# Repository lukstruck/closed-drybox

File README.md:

# closed-drybox
Open Source Filament Dry Box. But it's closed so it stays dry. Here are the plans, schematics and 3D Models needed.

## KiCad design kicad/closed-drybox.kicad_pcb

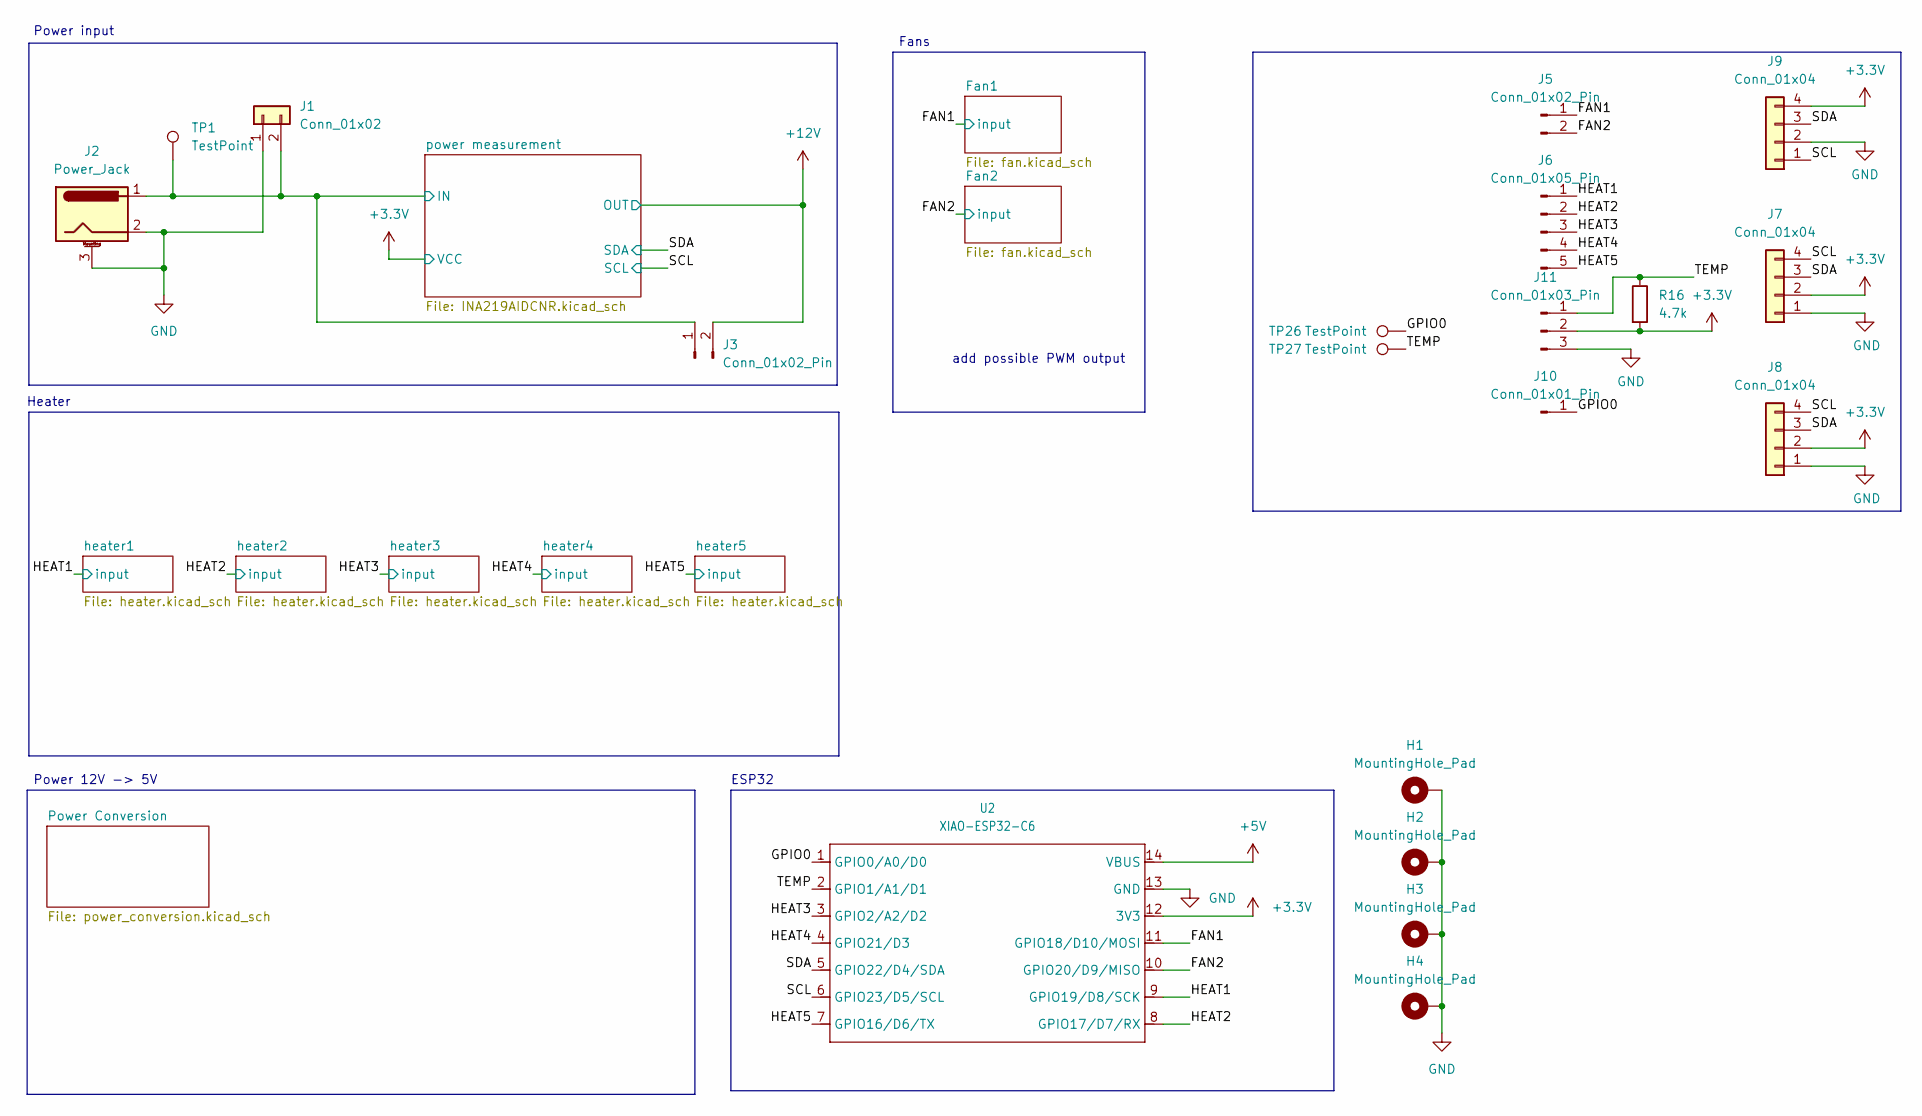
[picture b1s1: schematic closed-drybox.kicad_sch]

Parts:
H1, H2, H3, H4: MountingHole_Pad; MountingHole_3.2mm_M3_DIN965_Pad
J1: Conn_01x02; JST_XH_S2B-XH-A-1_1x02_P2.50mm_Horizontal; LCSC C157931
J2: Power_Jack; BarrelJack_Horizontal; LCSC C720558
J3, J5: Conn_01x02_Pin; PinHeader_1x02_P2.54mm_Vertical
J6: Conn_01x05_Pin; PinHeader_1x05_P2.54mm_Vertical
J7, J8, J9: Conn_01x04; JST_XH_B4B-XH-A_1x04_P2.50mm_Vertical
J10: Conn_01x01_Pin; PinHeader_1x01_P2.54mm_Vertical
J11: Conn_01x03_Pin; PinHeader_1x03_P2.54mm_Vertical
R16: 4.7k; R_0603_1608Metric_Pad0.98x0.95mm_HandSolder
TP1, TP26, TP27: TestPoint; TestPoint_Pad_D2.5mm
U2: XIAO-ESP32-C6; XIAO-ESP32C6-DIP

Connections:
+3.3V: J7.2, J8.2, J9.4, J11.2, R16.2, U2.12 (3V3); also elsewhere on the board
+5V: U2.14 (VBUS)
+12V: J3.2; also elsewhere on the board
/FAN1: J5.1, U2.11 (GPIO18/D10/MOSI); also elsewhere on the board
/FAN2: J5.2, U2.10 (GPIO20/D9/MISO); also elsewhere on the board
/GPIO0: J10.1, TP26.1, U2.1 (GPIO0/A0/D0)
/HEAT1: J6.1, U2.9 (GPIO19/D8/SCK); also elsewhere on the board
/HEAT2: J6.2, U2.8 (GPIO17/D7/RX); also elsewhere on the board
/HEAT3: J6.3, U2.3 (GPIO2/A2/D2); also elsewhere on the board
/HEAT4: J6.4, U2.4 (GPIO21/D3); also elsewhere on the board
/HEAT5: J6.5, U2.7 (GPIO16/D6/TX); also elsewhere on the board
/SCL: J7.4, J8.4, J9.1, U2.6 (GPIO23/D5/SCL); also elsewhere on the board
/SDA: J7.3, J8.3, J9.3, U2.5 (GPIO22/D4/SDA); also elsewhere on the board
/TEMP: J11.1, R16.1, TP27.1, U2.2 (GPIO1/A1/D1)
/power measurement/IN: J1.2, J2.1, J3.1, TP1.1; also elsewhere on the board
GND: H1.1, H2.1, H3.1, H4.1, J1.1, J2.2, J2.3 (MountPin), J7.1, J8.1, J9.2, J11.3, U2.13 (GND); also elsewhere on the board

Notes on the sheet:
add possible PWM output
Heater
ESP32
Power input
Power 12V -> 5V
Fans

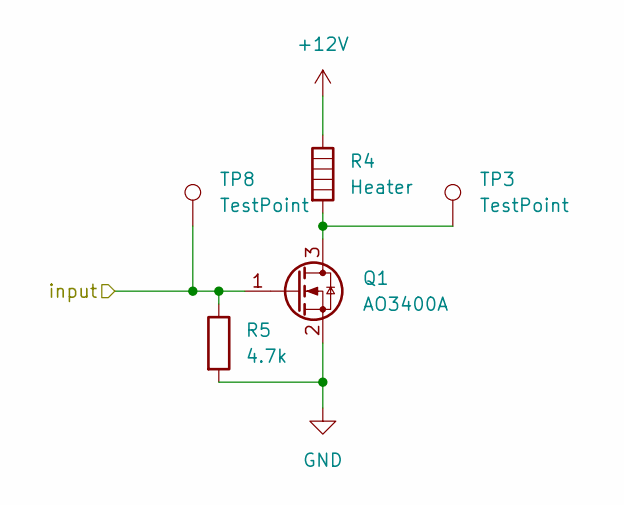
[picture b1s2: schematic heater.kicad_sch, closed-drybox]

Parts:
Q1: AO3400A; SOT-23; LCSC C20917
R4: Heater; JST_XH_S2B-XH-A_1x02_P2.50mm_Horizontal; LCSC C157931
R5: 4.7k; R_0603_1608Metric_Pad0.98x0.95mm_HandSolder
TP3, TP8: TestPoint; TestPoint_Pad_D2.5mm

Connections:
+12V: R4.1; also elsewhere on the board
/HEAT1: Q1.1 (G), R5.1, TP8.1; also elsewhere on the board
GND: Q1.2 (S), R5.2; also elsewhere on the board
unnamed: Q1.3 (D), R4.2, TP3.1

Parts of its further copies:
Q2, Q3, Q4, Q5: AO3400A; SOT-23; LCSC C20917
R6, R8, R10, R12: Heater; JST_XH_S2B-XH-A_1x02_P2.50mm_Horizontal; LCSC C157931
R7, R9, R11, R13: 4.7k; R_0603_1608Metric_Pad0.98x0.95mm_HandSolder
TP4, TP5, TP6, TP7, TP9, TP10, TP11, TP12: TestPoint; TestPoint_Pad_D2.5mm

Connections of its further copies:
+12V: R6.1, R8.1, R10.1, R12.1; also elsewhere on the board
/HEAT2: Q2.1 (G), R7.1, TP9.1; also elsewhere on the board
/HEAT3: Q3.1 (G), R9.1, TP10.1; also elsewhere on the board
/HEAT4: Q4.1 (G), R11.1, TP11.1; also elsewhere on the board
/HEAT5: Q5.1 (G), R13.1, TP12.1; also elsewhere on the board
GND: Q2.2 (S), Q3.2 (S), Q4.2 (S), Q5.2 (S), R7.2, R9.2, R11.2, R13.2; also elsewhere on the board
unnamed: Q2.3 (D), R6.2, TP4.1
unnamed: Q3.3 (D), R8.2, TP5.1
unnamed: Q4.3 (D), R10.2, TP6.1
unnamed: Q5.3 (D), R12.2, TP7.1

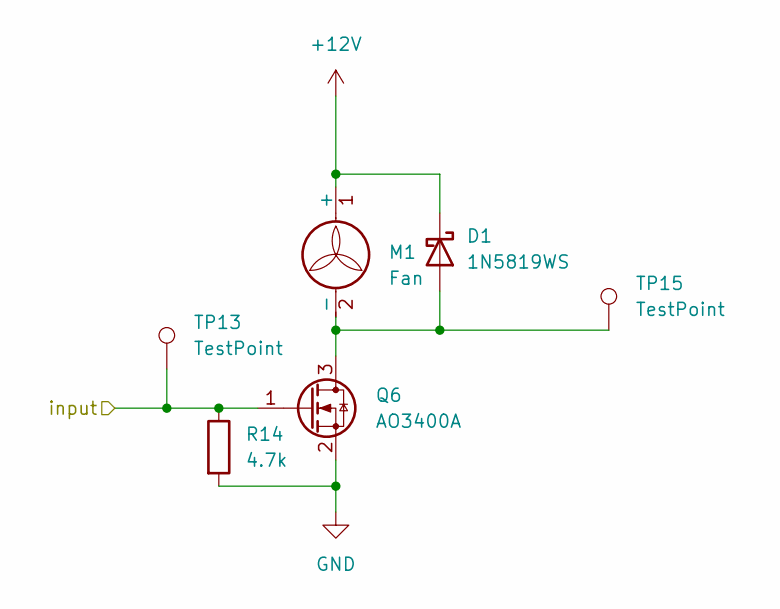
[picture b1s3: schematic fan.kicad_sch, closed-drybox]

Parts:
D1: 1N5819WS; D_SOD-323; LCSC C191023
M1: Fan; JST_XH_S2B-XH-A_1x02_P2.50mm_Horizontal; LCSC C157931
Q6: AO3400A; SOT-23; LCSC C20917
R14: 4.7k; R_0603_1608Metric_Pad0.98x0.95mm_HandSolder
TP13, TP15: TestPoint; TestPoint_Pad_D2.5mm

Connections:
+12V: D1.1 (K), M1.1 (+); also elsewhere on the board
/FAN1: Q6.1 (G), R14.1, TP13.1; also elsewhere on the board
GND: Q6.2 (S), R14.2; also elsewhere on the board
unnamed: D1.2 (A), M1.2 (-), Q6.3 (D), TP15.1

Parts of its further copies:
D2: 1N5819WS; D_SOD-323; LCSC C191023
M2: Fan; JST_XH_S2B-XH-A_1x02_P2.50mm_Horizontal; LCSC C157931
Q7: AO3400A; SOT-23; LCSC C20917
R15: 4.7k; R_0603_1608Metric_Pad0.98x0.95mm_HandSolder
TP14, TP16: TestPoint; TestPoint_Pad_D2.5mm

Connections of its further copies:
+12V: D2.1 (K), M2.1 (+); also elsewhere on the board
/FAN2: Q7.1 (G), R15.1, TP14.1; also elsewhere on the board
GND: Q7.2 (S), R15.2; also elsewhere on the board
unnamed: D2.2 (A), M2.2 (-), Q7.3 (D), TP16.1

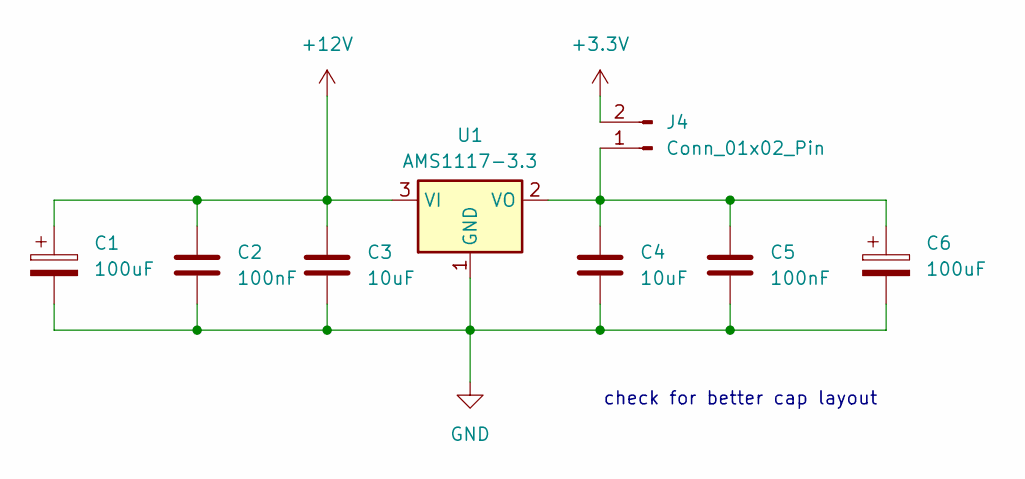
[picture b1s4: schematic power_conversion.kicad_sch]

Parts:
C1, C6: 100uF; C_0603_1608Metric
C2, C5: 100nF; C_0603_1608Metric; LCSC C14663
C3, C4: 10uF; C_0603_1608Metric; LCSC C96446
J4: Conn_01x02_Pin; PinHeader_1x02_P2.54mm_Vertical
U1: AMS1117-3.3; SOT-223-3_TabPin2

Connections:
+3.3V: J4.2; also elsewhere on the board
+12V: C1.1, C2.1, C3.1, U1.3 (VI); also elsewhere on the board
GND: C1.2, C2.2, C3.2, C4.2, C5.2, C6.2, U1.1 (GND); also elsewhere on the board
unnamed: C4.1, C5.1, C6.1, J4.1, U1.2 (VO)

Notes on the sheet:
check for better cap layout

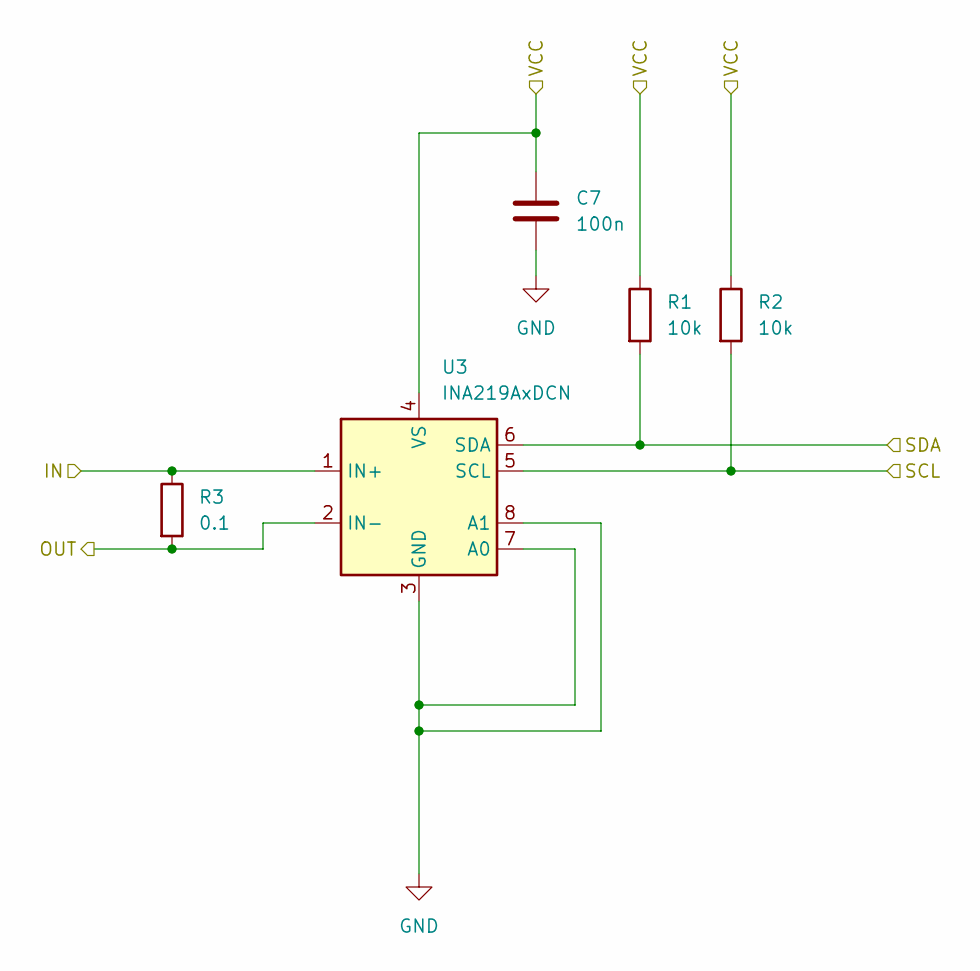
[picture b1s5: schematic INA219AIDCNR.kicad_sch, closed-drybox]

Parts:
C7: 100n; C_0603_1608Metric; LCSC C1591
R1, R2: 10k; R_0603_1608Metric; LCSC C25804
R3: 0.1; R_2512_6332Metric; LCSC C25466
U3: INA219AxDCN; SOT-23-8_Handsoldering; LCSC C87469

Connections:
+3.3V: C7.2, R1.1, R2.1, U3.4 (VS); also elsewhere on the board
+12V: R3.2, U3.2 (IN-); also elsewhere on the board
/SCL: R2.2, U3.5 (SCL); also elsewhere on the board
/SDA: R1.2, U3.6 (SDA); also elsewhere on the board
/power measurement/IN: R3.1, U3.1 (IN+); also elsewhere on the board
GND: C7.1, U3.3 (GND), U3.7 (A0), U3.8 (A1); also elsewhere on the board

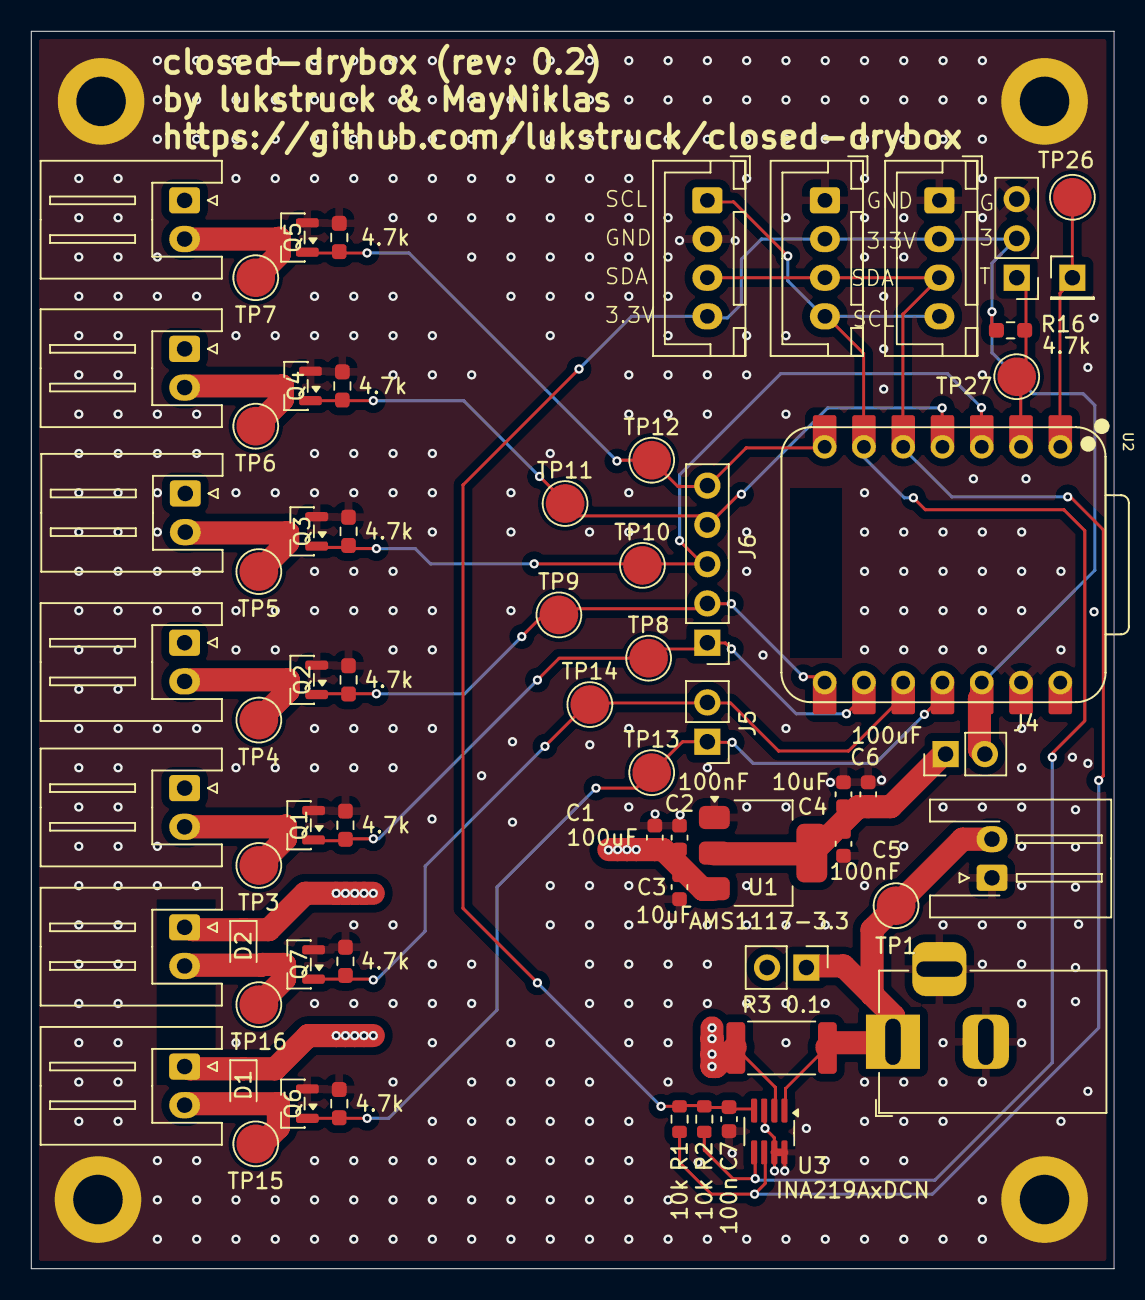
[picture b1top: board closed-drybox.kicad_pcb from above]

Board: 4 copper layers, 70.0 x 80.0 mm, 69 parts (0 on the bottom side), 23 nets.

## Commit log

2025-07-17 init kicad
2025-07-17 add 1117 3.3V
2025-07-17 add 1117 5V
2025-07-18 add #LCSC
2025-07-18 add Makefile
2025-07-18 add example
2025-07-18 correct Capacitators
2025-07-18 add seedstudio esp32-c6
2025-07-18 add esp32, add boxes
2025-07-19 add power messurement
2025-07-19 add anotations
2025-07-19 fix labels
2025-07-19 add diodes, fuse
2025-07-19 fix flyback diodes
2025-07-19 add part #'s
2025-07-20 add jumper for power
2025-07-20 add power jack symbol
2025-07-20 make switch passive
2025-10-15 add PCB
2025-10-30 add kibot workflows
2025-10-30 add deployment job
2025-11-03 update schematic
2025-12-02 added connectors
2025-12-02 added connectors to schematic
2025-12-03 added footprints
2025-12-30 pcb design v0.2
2025-12-31 review with @lukstruck
2025-12-31 change routing, fix capactitors, add pulldown resistors
2025-12-31 improve label placing, change footprints of connectors
2025-12-31 remove unnecessary labels
2026-01-23 remove mounting hole labels
2026-01-27 fix vias too close to each other
2026-01-27 add GND vias arround caps (next to LDO)
2026-05-07 3.3V LDO
2026-05-07 set project "closed-drybox"
2026-05-07 set LCSC ID's
